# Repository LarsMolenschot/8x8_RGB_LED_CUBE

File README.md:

# 8x8_RGB_LED_CUBE
This is a personal project, the goal of the project is to create a RGB LED cube with the AA0084 RGB LED's.
A custom PCB will be designed for the cube housing a STM32 which can be programmed to display different patterns.
The PCB will include a expansion possibility to house a sd card slot with spi in the future.

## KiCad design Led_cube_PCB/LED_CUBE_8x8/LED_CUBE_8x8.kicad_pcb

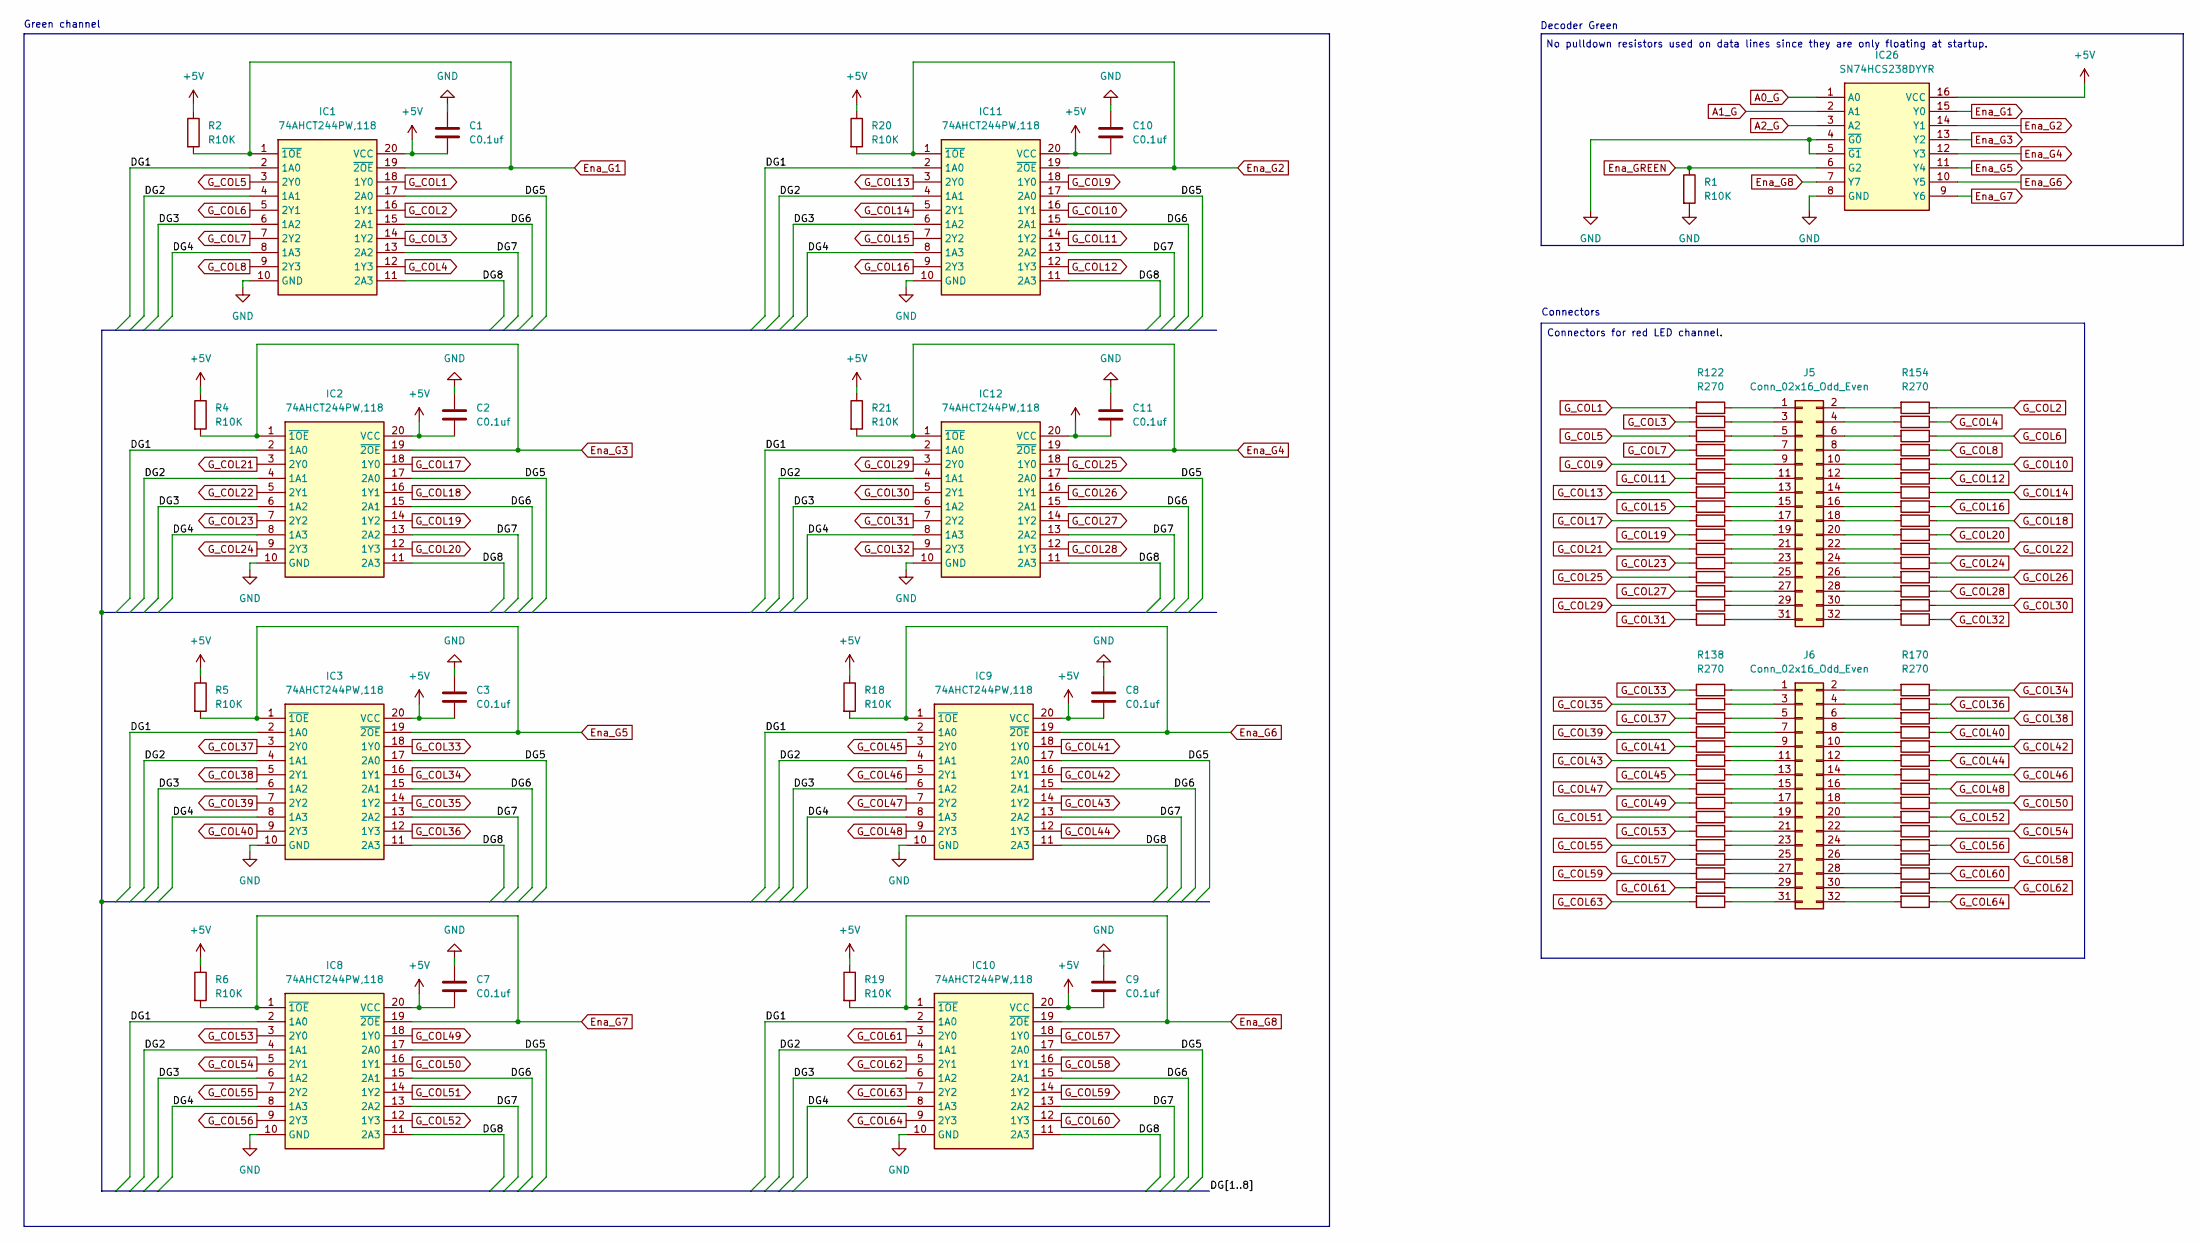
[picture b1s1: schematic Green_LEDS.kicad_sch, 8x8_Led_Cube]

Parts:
C1, C2, C3, C7, C8, C9, C10, C11: C0.1uf; C_0603_1608Metric_Pad1.08x0.95mm_HandSolder
IC1, IC2, IC3, IC8, IC9, IC10, IC11, IC12: 74AHCT244PW,118; SOP65P640X110-20N; Mouser Part Number 771-AHCT244PW118
IC26: SN74HCS238DYYR; SOP50P326X110-16N; Mouser Part Number 595-SN74HCS238DYYR
J5, J6: Conn_02x16_Odd_Even; PinSocket_2x16_P2.54mm_Vertical
R1, R2, R4, R5, R6, R18, R19, R20, R21: R10K; R_0603_1608Metric_Pad0.98x0.95mm_HandSolder
R122, R123, R124, R125, R126, R127, R128, R129, R130, R131, R132, R133, R134, R135, R136, R137, R138, R139, R140, R141, R142, R143, R144, R145, R146, R147, R148, R149, R150, R151, R152, R153, R154, R155, R156, R157, R158, R159, R160, R161, R162, R163, R164, R165, R166, R167, R168, R169, R170, R171, R172, R173, R174, R175, R176, R177, R178, R179, R180, R181, R182, R183, R184, R185: R270; R_0603_1608Metric_Pad0.98x0.95mm_HandSolder

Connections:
+5V: C1.2, C2.2, C3.2, C7.2, C8.2, C9.2, C10.2, C11.2, IC1.20 (VCC), IC2.20 (VCC), IC3.20 (VCC), IC8.20 (VCC), IC9.20 (VCC), IC10.20 (VCC), IC11.20 (VCC), IC12.20 (VCC), IC26.16 (VCC), R2.1, R4.1, R5.1, R6.1, R18.1, R19.1, R20.1, R21.1; also elsewhere on the board
/Green LED's/DG1: IC1.2 (1A0), IC2.2 (1A0), IC3.2 (1A0), IC8.2 (1A0), IC9.2 (1A0), IC10.2 (1A0), IC11.2 (1A0), IC12.2 (1A0)
/Green LED's/DG2: IC1.4 (1A1), IC2.4 (1A1), IC3.4 (1A1), IC8.4 (1A1), IC9.4 (1A1), IC10.4 (1A1), IC11.4 (1A1), IC12.4 (1A1)
/Green LED's/DG3: IC1.6 (1A2), IC2.6 (1A2), IC3.6 (1A2), IC8.6 (1A2), IC9.6 (1A2), IC10.6 (1A2), IC11.6 (1A2), IC12.6 (1A2)
/Green LED's/DG4: IC1.8 (1A3), IC2.8 (1A3), IC3.8 (1A3), IC8.8 (1A3), IC9.8 (1A3), IC10.8 (1A3), IC11.8 (1A3), IC12.8 (1A3)
/Green LED's/DG5: IC1.17 (2A0), IC2.17 (2A0), IC3.17 (2A0), IC8.17 (2A0), IC9.17 (2A0), IC10.17 (2A0), IC11.17 (2A0), IC12.17 (2A0)
/Green LED's/DG6: IC1.15 (2A1), IC2.15 (2A1), IC3.15 (2A1), IC8.15 (2A1), IC9.15 (2A1), IC10.15 (2A1), IC11.15 (2A1), IC12.15 (2A1)
/Green LED's/DG7: IC1.13 (2A2), IC2.13 (2A2), IC3.13 (2A2), IC8.13 (2A2), IC9.13 (2A2), IC10.13 (2A2), IC11.13 (2A2), IC12.13 (2A2)
/Green LED's/DG8: IC1.11 (2A3), IC2.11 (2A3), IC3.11 (2A3), IC8.11 (2A3), IC9.11 (2A3), IC10.11 (2A3), IC11.11 (2A3), IC12.11 (2A3)
A0_G: IC26.1 (A0); also elsewhere on the board
A1_G: IC26.2 (A1); also elsewhere on the board
A2_G: IC26.3 (A2); also elsewhere on the board
Ena_G1: IC1.1 (~1OE), IC1.19 (~2OE), IC26.15 (Y0), R2.2
Ena_G2: IC11.1 (~1OE), IC11.19 (~2OE), IC26.14 (Y1), R20.2
Ena_G3: IC2.1 (~1OE), IC2.19 (~2OE), IC26.13 (Y2), R4.2
Ena_G4: IC12.1 (~1OE), IC12.19 (~2OE), IC26.12 (Y3), R21.2
Ena_G5: IC3.1 (~1OE), IC3.19 (~2OE), IC26.11 (Y4), R5.2
Ena_G6: IC9.1 (~1OE), IC9.19 (~2OE), IC26.10 (Y5), R18.2
Ena_G7: IC8.1 (~1OE), IC8.19 (~2OE), IC26.9 (Y6), R6.2
Ena_G8: IC10.1 (~1OE), IC10.19 (~2OE), IC26.7 (Y7), R19.2
Ena_GREEN: IC26.6 (G2), R1.1
GND: C1.1, C2.1, C3.1, C7.1, C8.1, C9.1, C10.1, C11.1, IC1.10 (GND), IC2.10 (GND), IC3.10 (GND), IC8.10 (GND), IC9.10 (GND), IC10.10 (GND), IC11.10 (GND), IC12.10 (GND), IC26.4 (~G0), IC26.5 (~G1), IC26.8 (GND), R1.2; also elsewhere on the board
G_COL1: IC1.18 (1Y0), R122.2
G_COL2: IC1.16 (1Y1), R154.1
G_COL3: IC1.14 (1Y2), R123.2
G_COL4: IC1.12 (1Y3), R155.1
G_COL5: IC1.3 (2Y0), R124.2
G_COL6: IC1.5 (2Y1), R156.1
G_COL7: IC1.7 (2Y2), R125.2
G_COL8: IC1.9 (2Y3), R157.1
G_COL9: IC11.18 (1Y0), R126.2
G_COL10: IC11.16 (1Y1), R158.1
G_COL11: IC11.14 (1Y2), R127.2
G_COL12: IC11.12 (1Y3), R159.1
G_COL13: IC11.3 (2Y0), R128.2
G_COL14: IC11.5 (2Y1), R160.1
G_COL15: IC11.7 (2Y2), R129.2
G_COL16: IC11.9 (2Y3), R161.1
G_COL17: IC2.18 (1Y0), R130.2
G_COL18: IC2.16 (1Y1), R162.1
G_COL19: IC2.14 (1Y2), R131.2
G_COL20: IC2.12 (1Y3), R163.1
G_COL21: IC2.3 (2Y0), R132.2
G_COL22: IC2.5 (2Y1), R164.1
G_COL23: IC2.7 (2Y2), R133.2
G_COL24: IC2.9 (2Y3), R165.1
G_COL25: IC12.18 (1Y0), R134.2
G_COL26: IC12.16 (1Y1), R166.1
G_COL27: IC12.14 (1Y2), R135.2
G_COL28: IC12.12 (1Y3), R167.1
G_COL29: IC12.3 (2Y0), R136.2
G_COL30: IC12.5 (2Y1), R168.1
G_COL31: IC12.7 (2Y2), R137.2
G_COL32: IC12.9 (2Y3), R169.1
G_COL33: IC3.18 (1Y0), R138.2
G_COL34: IC3.16 (1Y1), R170.1
G_COL35: IC3.14 (1Y2), R139.2
G_COL36: IC3.12 (1Y3), R171.1
G_COL37: IC3.3 (2Y0), R140.2
G_COL38: IC3.5 (2Y1), R172.1
G_COL39: IC3.7 (2Y2), R141.2
G_COL40: IC3.9 (2Y3), R173.1
G_COL41: IC9.18 (1Y0), R142.2
G_COL42: IC9.16 (1Y1), R174.1
G_COL43: IC9.14 (1Y2), R143.2
G_COL44: IC9.12 (1Y3), R175.1
G_COL45: IC9.3 (2Y0), R144.2
G_COL46: IC9.5 (2Y1), R176.1
G_COL47: IC9.7 (2Y2), R145.2
G_COL48: IC9.9 (2Y3), R177.1
G_COL49: IC8.18 (1Y0), R146.2
G_COL50: IC8.16 (1Y1), R178.1
G_COL51: IC8.14 (1Y2), R147.2
G_COL52: IC8.12 (1Y3), R179.1
G_COL53: IC8.3 (2Y0), R148.2
G_COL54: IC8.5 (2Y1), R180.1
G_COL55: IC8.7 (2Y2), R149.2
G_COL56: IC8.9 (2Y3), R181.1
G_COL57: IC10.18 (1Y0), R150.2
G_COL58: IC10.16 (1Y1), R182.1
G_COL59: IC10.14 (1Y2), R151.2
G_COL60: IC10.12 (1Y3), R183.1
G_COL61: IC10.3 (2Y0), R152.2
G_COL62: IC10.5 (2Y1), R184.1
G_COL63: IC10.7 (2Y2), R153.2
G_COL64: IC10.9 (2Y3), R185.1
unnamed: J5.1, R122.1
unnamed: J5.2, R154.2
unnamed: J5.3, R123.1
unnamed: J5.4, R155.2
unnamed: J5.5, R124.1
unnamed: J5.6, R156.2
unnamed: J5.7, R125.1
unnamed: J5.8, R157.2
unnamed: J5.9, R126.1
unnamed: J5.10, R158.2
unnamed: J5.11, R127.1
unnamed: J5.12, R159.2
unnamed: J5.13, R128.1
unnamed: J5.14, R160.2
unnamed: J5.15, R129.1
unnamed: J5.16, R161.2
unnamed: J5.17, R130.1
unnamed: J5.18, R162.2
unnamed: J5.19, R131.1
unnamed: J5.20, R163.2
unnamed: J5.21, R132.1
unnamed: J5.22, R164.2
unnamed: J5.23, R133.1
unnamed: J5.24, R165.2
unnamed: J5.25, R134.1
unnamed: J5.26, R166.2
unnamed: J5.27, R135.1
unnamed: J5.28, R167.2
unnamed: J5.29, R136.1
unnamed: J5.30, R168.2
unnamed: J5.31, R137.1
unnamed: J5.32, R169.2
unnamed: J6.1, R138.1
unnamed: J6.2, R170.2
unnamed: J6.3, R139.1
unnamed: J6.4, R171.2
unnamed: J6.5, R140.1
unnamed: J6.6, R172.2
unnamed: J6.7, R141.1
unnamed: J6.8, R173.2
unnamed: J6.9, R142.1
unnamed: J6.10, R174.2
unnamed: J6.11, R143.1
unnamed: J6.12, R175.2
unnamed: J6.13, R144.1
unnamed: J6.14, R176.2
unnamed: J6.15, R145.1
unnamed: J6.16, R177.2
unnamed: J6.17, R146.1
unnamed: J6.18, R178.2
unnamed: J6.19, R147.1
unnamed: J6.20, R179.2
unnamed: J6.21, R148.1
unnamed: J6.22, R180.2
unnamed: J6.23, R149.1
unnamed: J6.24, R181.2
unnamed: J6.25, R150.1
unnamed: J6.26, R182.2
unnamed: J6.27, R151.1
unnamed: J6.28, R183.2
unnamed: J6.29, R152.1
unnamed: J6.30, R184.2
unnamed: J6.31, R153.1
unnamed: J6.32, R185.2

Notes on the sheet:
Connectors
Decoder Green
No pulldown resistors used on data lines since they are only floating at startup.
Green channel
Connectors for red LED channel.

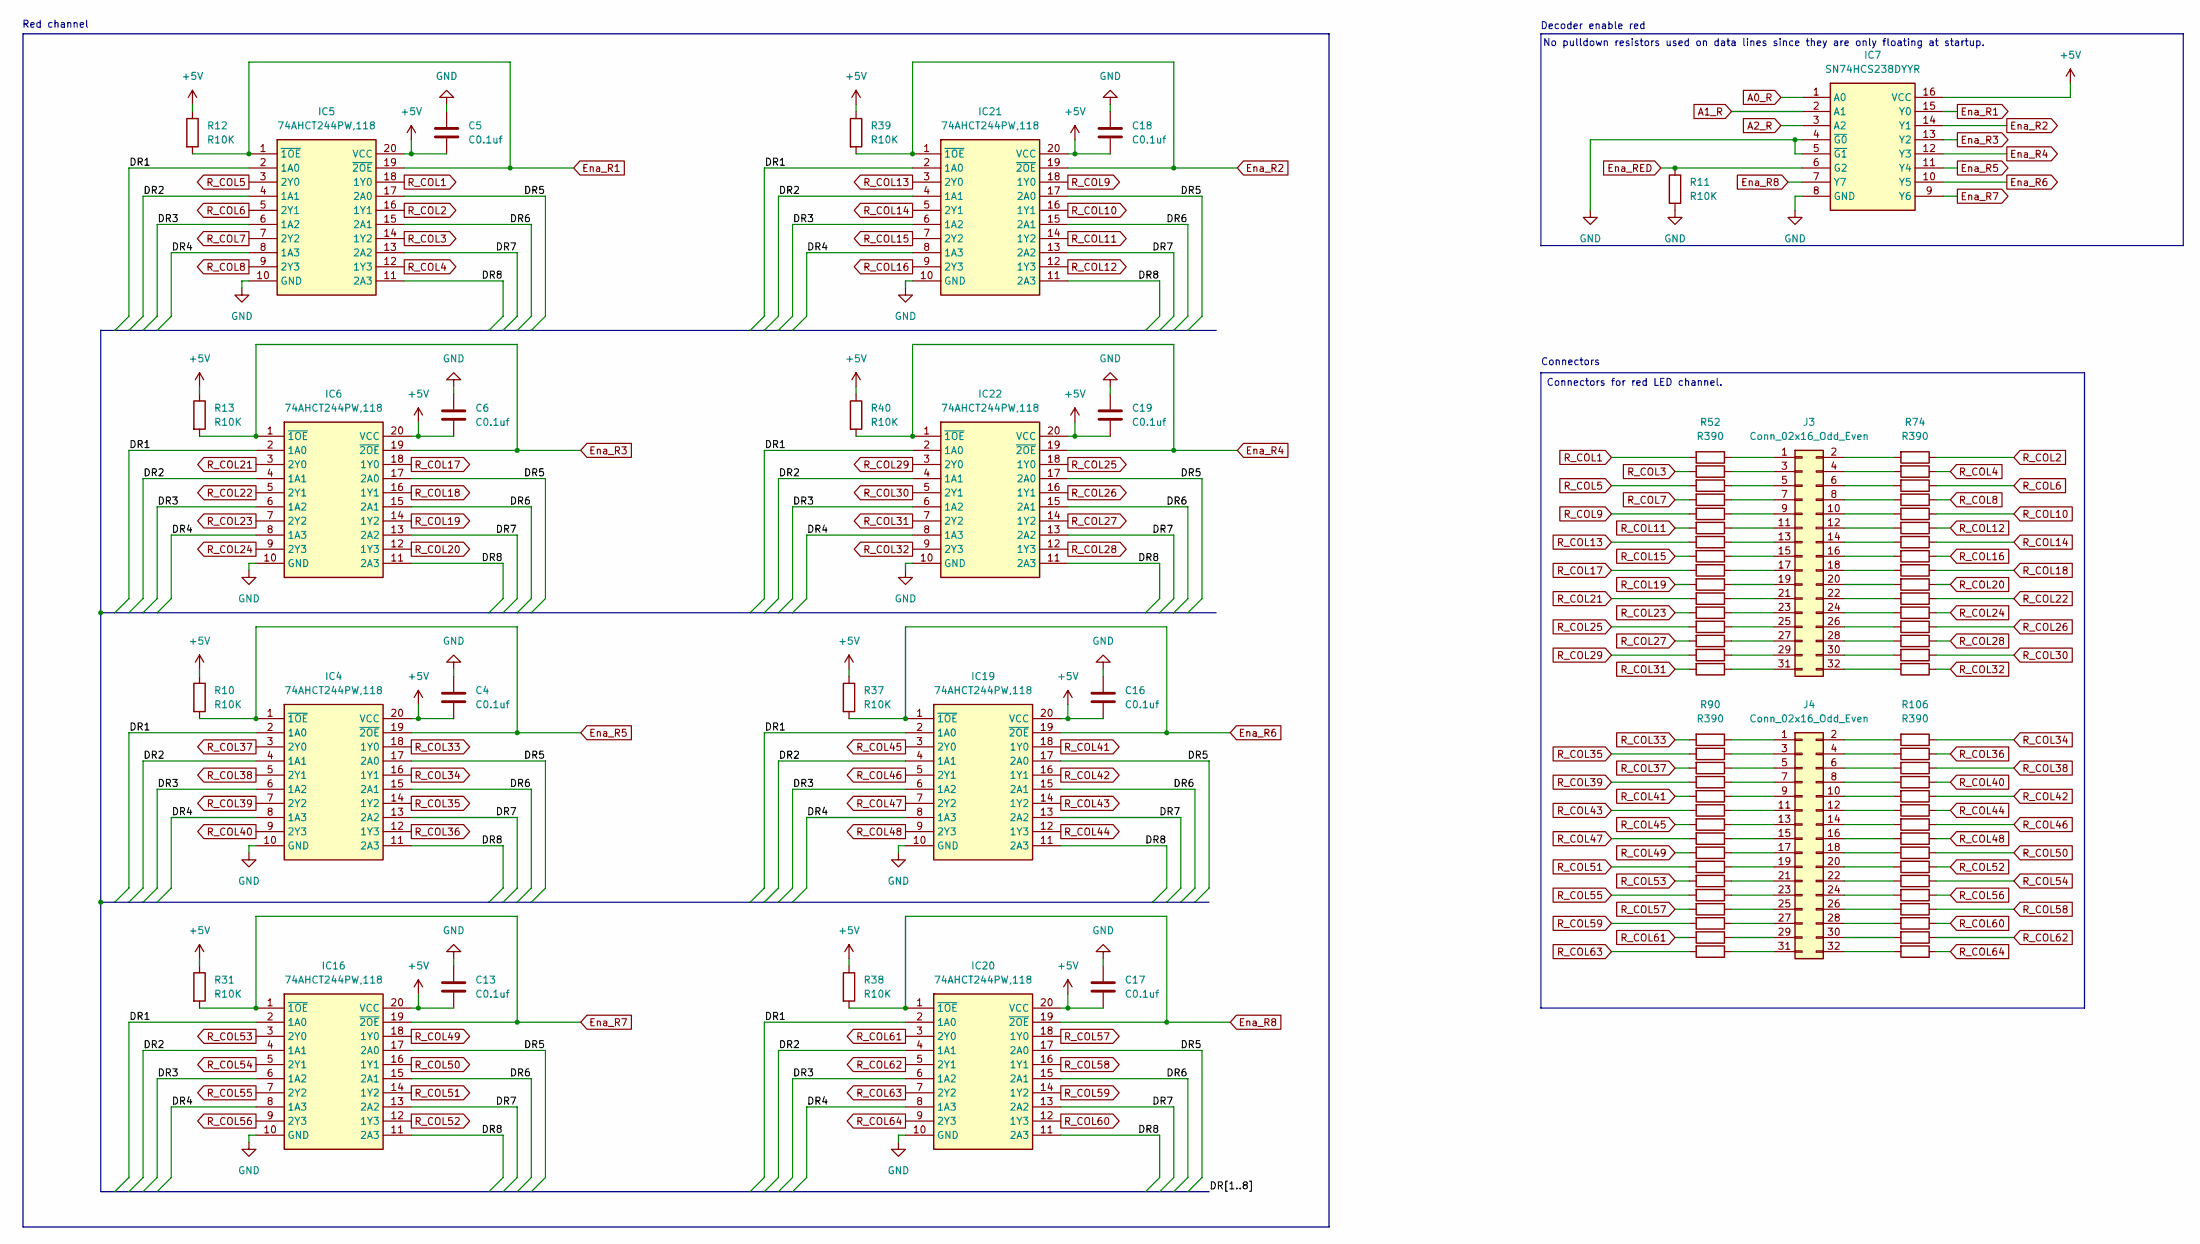
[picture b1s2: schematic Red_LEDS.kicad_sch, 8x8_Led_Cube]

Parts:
C4, C5, C6, C13, C16, C17, C18, C19: C0.1uf; C_0603_1608Metric_Pad1.08x0.95mm_HandSolder
IC4, IC5, IC6, IC16, IC19, IC20, IC21, IC22: 74AHCT244PW,118; SOP65P640X110-20N; Mouser Part Number 771-AHCT244PW118
IC7: SN74HCS238DYYR; SOP50P326X110-16N; Mouser Part Number 595-SN74HCS238DYYR
J3, J4: Conn_02x16_Odd_Even; PinSocket_2x16_P2.54mm_Vertical
R10, R11, R12, R13, R31, R37, R38, R39, R40: R10K; R_0603_1608Metric_Pad0.98x0.95mm_HandSolder
R52, R53, R60, R61, R62, R63, R64, R65, R66, R67, R68, R69, R70, R71, R72, R73, R74, R75, R76, R77, R78, R79, R80, R81, R82, R83, R84, R85, R86, R87, R88, R89, R90, R91, R92, R93, R94, R95, R96, R97, R98, R99, R100, R101, R102, R103, R104, R105, R106, R107, R108, R109, R110, R111, R112, R113, R114, R115, R116, R117, R118, R119, R120, R121: R390; R_0603_1608Metric_Pad0.98x0.95mm_HandSolder

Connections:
+5V: C4.2, C5.2, C6.2, C13.2, C16.2, C17.2, C18.2, C19.2, IC4.20 (VCC), IC5.20 (VCC), IC6.20 (VCC), IC7.16 (VCC), IC16.20 (VCC), IC19.20 (VCC), IC20.20 (VCC), IC21.20 (VCC), IC22.20 (VCC), R10.1, R12.1, R13.1, R31.1, R37.1, R38.1, R39.1, R40.1; also elsewhere on the board
/Red LED's/DR1: IC4.2 (1A0), IC5.2 (1A0), IC6.2 (1A0), IC16.2 (1A0), IC19.2 (1A0), IC20.2 (1A0), IC21.2 (1A0), IC22.2 (1A0)
/Red LED's/DR2: IC4.4 (1A1), IC5.4 (1A1), IC6.4 (1A1), IC16.4 (1A1), IC19.4 (1A1), IC20.4 (1A1), IC21.4 (1A1), IC22.4 (1A1)
/Red LED's/DR3: IC4.6 (1A2), IC5.6 (1A2), IC6.6 (1A2), IC16.6 (1A2), IC19.6 (1A2), IC20.6 (1A2), IC21.6 (1A2), IC22.6 (1A2)
/Red LED's/DR4: IC4.8 (1A3), IC5.8 (1A3), IC6.8 (1A3), IC16.8 (1A3), IC19.8 (1A3), IC20.8 (1A3), IC21.8 (1A3), IC22.8 (1A3)
/Red LED's/DR5: IC4.17 (2A0), IC5.17 (2A0), IC6.17 (2A0), IC16.17 (2A0), IC19.17 (2A0), IC20.17 (2A0), IC21.17 (2A0), IC22.17 (2A0)
/Red LED's/DR6: IC4.15 (2A1), IC5.15 (2A1), IC6.15 (2A1), IC16.15 (2A1), IC19.15 (2A1), IC20.15 (2A1), IC21.15 (2A1), IC22.15 (2A1)
/Red LED's/DR7: IC4.13 (2A2), IC5.13 (2A2), IC6.13 (2A2), IC16.13 (2A2), IC19.13 (2A2), IC20.13 (2A2), IC21.13 (2A2), IC22.13 (2A2)
/Red LED's/DR8: IC4.11 (2A3), IC5.11 (2A3), IC6.11 (2A3), IC16.11 (2A3), IC19.11 (2A3), IC20.11 (2A3), IC21.11 (2A3), IC22.11 (2A3)
A0_R: IC7.1 (A0); also elsewhere on the board
A1_R: IC7.2 (A1); also elsewhere on the board
A2_R: IC7.3 (A2); also elsewhere on the board
Ena_R1: IC5.1 (~1OE), IC5.19 (~2OE), IC7.15 (Y0), R12.2
Ena_R2: IC7.14 (Y1), IC21.1 (~1OE), IC21.19 (~2OE), R39.2
Ena_R3: IC6.1 (~1OE), IC6.19 (~2OE), IC7.13 (Y2), R13.2
Ena_R4: IC7.12 (Y3), IC22.1 (~1OE), IC22.19 (~2OE), R40.2
Ena_R5: IC4.1 (~1OE), IC4.19 (~2OE), IC7.11 (Y4), R10.2
Ena_R6: IC7.10 (Y5), IC19.1 (~1OE), IC19.19 (~2OE), R37.2
Ena_R7: IC7.9 (Y6), IC16.1 (~1OE), IC16.19 (~2OE), R31.2
Ena_R8: IC7.7 (Y7), IC20.1 (~1OE), IC20.19 (~2OE), R38.2
Ena_RED: IC7.6 (G2), R11.1
GND: C4.1, C5.1, C6.1, C13.1, C16.1, C17.1, C18.1, C19.1, IC4.10 (GND), IC5.10 (GND), IC6.10 (GND), IC7.4 (~G0), IC7.5 (~G1), IC7.8 (GND), IC16.10 (GND), IC19.10 (GND), IC20.10 (GND), IC21.10 (GND), IC22.10 (GND), R11.2; also elsewhere on the board
unnamed: J3.1, R52.1
unnamed: J3.2, R74.2
unnamed: J3.3, R53.1
unnamed: J3.4, R75.2
unnamed: J3.5, R60.1
unnamed: J3.6, R76.2
unnamed: J3.7, R61.1
unnamed: J3.8, R77.2
unnamed: J3.9, R62.1
unnamed: J3.10, R78.2
unnamed: J3.11, R63.1
unnamed: J3.12, R79.2
unnamed: J3.13, R64.1
unnamed: J3.14, R80.2
unnamed: J3.15, R65.1
unnamed: J3.16, R81.2
unnamed: J3.17, R66.1
unnamed: J3.18, R82.2
unnamed: J3.19, R67.1
unnamed: J3.20, R83.2
unnamed: J3.21, R68.1
unnamed: J3.22, R84.2
unnamed: J3.23, R69.1
unnamed: J3.24, R85.2
unnamed: J3.25, R70.1
unnamed: J3.26, R86.2
unnamed: J3.27, R71.1
unnamed: J3.28, R87.2
unnamed: J3.29, R72.1
unnamed: J3.30, R88.2
unnamed: J3.31, R73.1
unnamed: J3.32, R89.2
unnamed: J4.1, R90.1
unnamed: J4.2, R106.2
unnamed: J4.3, R91.1
unnamed: J4.4, R107.2
unnamed: J4.5, R92.1
unnamed: J4.6, R108.2
unnamed: J4.7, R93.1
unnamed: J4.8, R109.2
unnamed: J4.9, R94.1
unnamed: J4.10, R110.2
unnamed: J4.11, R95.1
unnamed: J4.12, R111.2
unnamed: J4.13, R96.1
unnamed: J4.14, R112.2
unnamed: J4.15, R97.1
unnamed: J4.16, R113.2
unnamed: J4.17, R98.1
unnamed: J4.18, R114.2
unnamed: J4.19, R99.1
unnamed: J4.20, R115.2
unnamed: J4.21, R100.1
unnamed: J4.22, R116.2
unnamed: J4.23, R101.1
unnamed: J4.24, R117.2
unnamed: J4.25, R102.1
unnamed: J4.26, R118.2
unnamed: J4.27, R103.1
unnamed: J4.28, R119.2
unnamed: J4.29, R104.1
unnamed: J4.30, R120.2
unnamed: J4.31, R105.1
unnamed: J4.32, R121.2
R_COL1: IC5.18 (1Y0), R52.2
R_COL2: IC5.16 (1Y1), R74.1
R_COL3: IC5.14 (1Y2), R53.2
R_COL4: IC5.12 (1Y3), R75.1
R_COL5: IC5.3 (2Y0), R60.2
R_COL6: IC5.5 (2Y1), R76.1
R_COL7: IC5.7 (2Y2), R61.2
R_COL8: IC5.9 (2Y3), R77.1
R_COL9: IC21.18 (1Y0), R62.2
R_COL10: IC21.16 (1Y1), R78.1
R_COL11: IC21.14 (1Y2), R63.2
R_COL12: IC21.12 (1Y3), R79.1
R_COL13: IC21.3 (2Y0), R64.2
R_COL14: IC21.5 (2Y1), R80.1
R_COL15: IC21.7 (2Y2), R65.2
R_COL16: IC21.9 (2Y3), R81.1
R_COL17: IC6.18 (1Y0), R66.2
R_COL18: IC6.16 (1Y1), R82.1
R_COL19: IC6.14 (1Y2), R67.2
R_COL20: IC6.12 (1Y3), R83.1
R_COL21: IC6.3 (2Y0), R68.2
R_COL22: IC6.5 (2Y1), R84.1
R_COL23: IC6.7 (2Y2), R69.2
R_COL24: IC6.9 (2Y3), R85.1
R_COL25: IC22.18 (1Y0), R70.2
R_COL26: IC22.16 (1Y1), R86.1
R_COL27: IC22.14 (1Y2), R71.2
R_COL28: IC22.12 (1Y3), R87.1
R_COL29: IC22.3 (2Y0), R72.2
R_COL30: IC22.5 (2Y1), R88.1
R_COL31: IC22.7 (2Y2), R73.2
R_COL32: IC22.9 (2Y3), R89.1
R_COL33: IC4.18 (1Y0), R90.2
R_COL34: IC4.16 (1Y1), R106.1
R_COL35: IC4.14 (1Y2), R91.2
R_COL36: IC4.12 (1Y3), R107.1
R_COL37: IC4.3 (2Y0), R92.2
R_COL38: IC4.5 (2Y1), R108.1
R_COL39: IC4.7 (2Y2), R93.2
R_COL40: IC4.9 (2Y3), R109.1
R_COL41: IC19.18 (1Y0), R94.2
R_COL42: IC19.16 (1Y1), R110.1
R_COL43: IC19.14 (1Y2), R95.2
R_COL44: IC19.12 (1Y3), R111.1
R_COL45: IC19.3 (2Y0), R96.2
R_COL46: IC19.5 (2Y1), R112.1
R_COL47: IC19.7 (2Y2), R97.2
R_COL48: IC19.9 (2Y3), R113.1
R_COL49: IC16.18 (1Y0), R98.2
R_COL50: IC16.16 (1Y1), R114.1
R_COL51: IC16.14 (1Y2), R99.2
R_COL52: IC16.12 (1Y3), R115.1
R_COL53: IC16.3 (2Y0), R100.2
R_COL54: IC16.5 (2Y1), R116.1
R_COL55: IC16.7 (2Y2), R101.2
R_COL56: IC16.9 (2Y3), R117.1
R_COL57: IC20.18 (1Y0), R102.2
R_COL58: IC20.16 (1Y1), R118.1
R_COL59: IC20.14 (1Y2), R103.2
R_COL60: IC20.12 (1Y3), R119.1
R_COL61: IC20.3 (2Y0), R104.2
R_COL62: IC20.5 (2Y1), R120.1
R_COL63: IC20.7 (2Y2), R105.2
R_COL64: IC20.9 (2Y3), R121.1

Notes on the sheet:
Connectors
Red channel
No pulldown resistors used on data lines since they are only floating at startup.
Decoder enable red
Connectors for red LED channel.

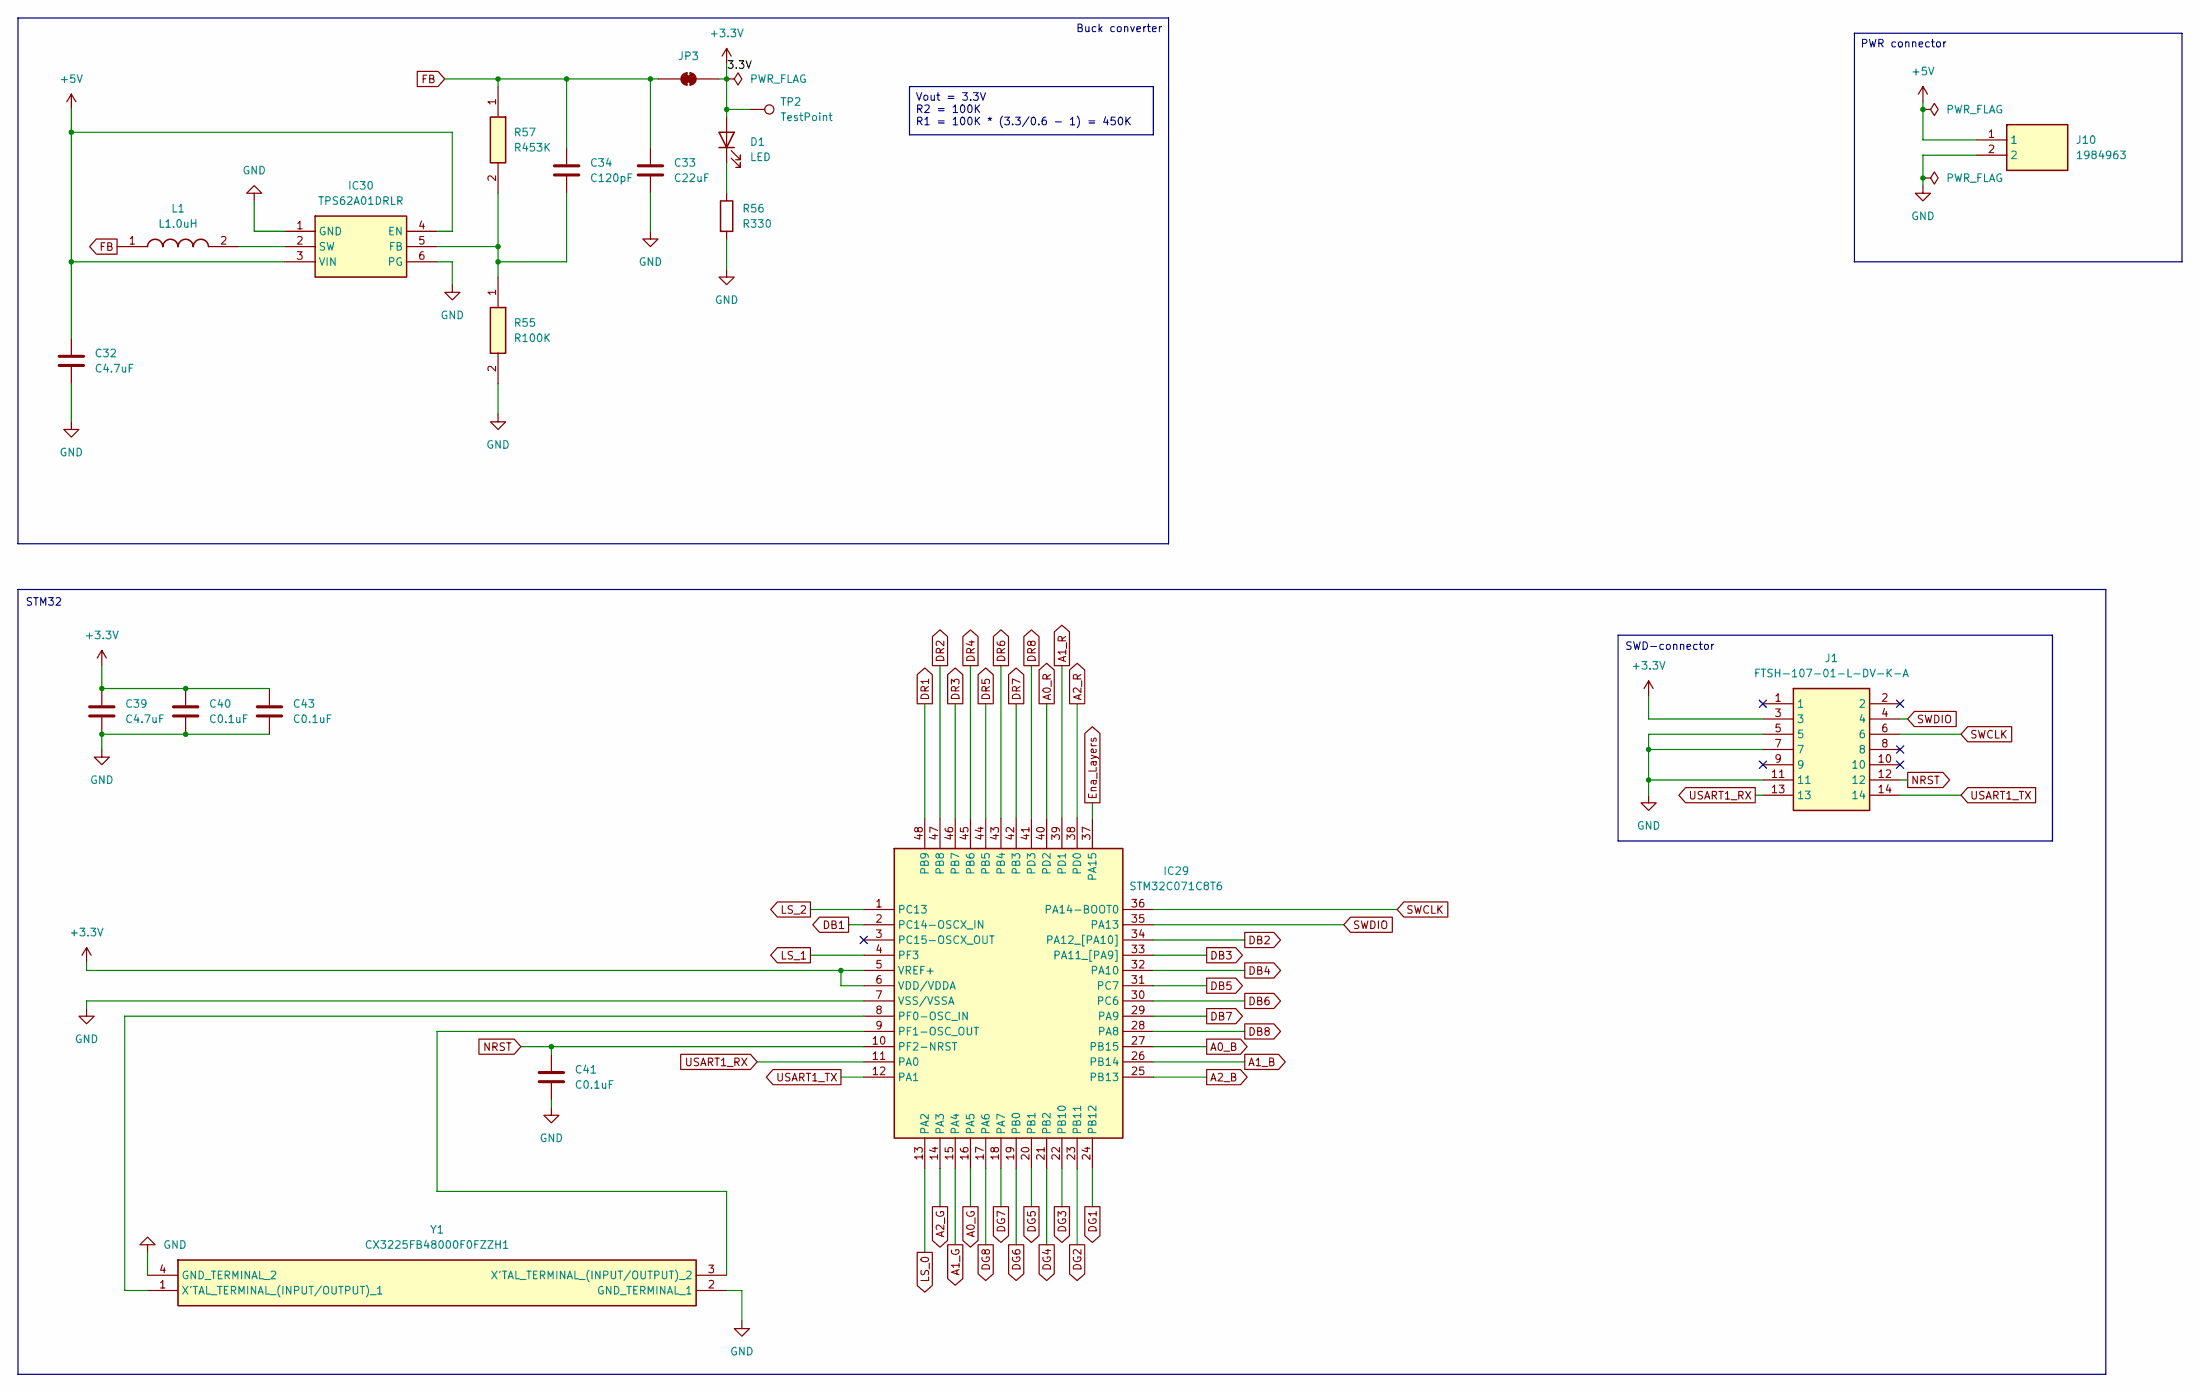
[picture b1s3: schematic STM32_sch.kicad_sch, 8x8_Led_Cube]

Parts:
C32, C39: C4.7uF; C_0603_1608Metric_Pad1.08x0.95mm_HandSolder
C33: C22uF; C_0603_1608Metric_Pad1.08x0.95mm_HandSolder
C34: C120pF; C_0603_1608Metric_Pad1.08x0.95mm_HandSolder
C40, C41, C43: C0.1uF; C_0603_1608Metric_Pad1.08x0.95mm_HandSolder
D1: LED; LED_0805_2012Metric_Pad1.15x1.40mm_HandSolder
IC29: STM32C071C8T6; QFP50P900X900X160-48N; Mouser Part Number 511-STM32C071C8T6
IC30: TPS62A01DRLR; SOTFL50P160X60-6N; Mouser Part Number 595-TPS62A01DRLR
J1: FTSH-107-01-L-DV-K-A; FTSH-107-XX-YYY-DV-K-A; Mouser Part Number 200-FTSH10701LDVKA
J10: 1984963; Mouser Part Number 651-1984963
JP3: SolderJumper_2_Bridged; SolderJumper-2_P1.3mm_Open_RoundedPad1.0x1.5mm
L1: L1.0uH; DFE2HCAH1R0MJ0L; Mouser Part Number 81-DFE252012F-1R0MP2
R55: R100K; R_0603_1608Metric_Pad0.98x0.95mm_HandSolder; Mouser Part Number 603-SR0603FR-07100KL
R56: R330; R_0603_1608Metric_Pad0.98x0.95mm_HandSolder
R57: R453K; R_0603_1608Metric_Pad0.98x0.95mm_HandSolder; Mouser Part Number 603-AF0603FR-07453KL
TP2: TestPoint; TestPoint_Pad_D2.0mm
Y1: CX3225FB48000F0FZZH1; Manufacturer_Part_Number CX3225FB48000F0FZZH1

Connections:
+3.3V: C39.1, C40.1, C43.1, D1.2 (A), IC29.5 (VREF+), IC29.6 (VDD/VDDA), J1.3, JP3.1 (A), TP2.1 (1_1); also elsewhere on the board
+5V: C32.1, IC30.3 (VIN), IC30.4 (EN), J10.1; also elsewhere on the board
A0_B: IC29.27 (PB15); also elsewhere on the board
A0_G: IC29.16 (PA5); also elsewhere on the board
A0_R: IC29.40 (PD2); also elsewhere on the board
A1_B: IC29.26 (PB14); also elsewhere on the board
A1_G: IC29.15 (PA4); also elsewhere on the board
A1_R: IC29.39 (PD1); also elsewhere on the board
A2_B: IC29.25 (PB13); also elsewhere on the board
A2_G: IC29.14 (PA3); also elsewhere on the board
A2_R: IC29.38 (PD0); also elsewhere on the board
DB1: IC29.2 (PC14-OSCX_IN)
DB2: IC29.34 (PA12_[PA10])
DB3: IC29.33 (PA11_[PA9])
DB4: IC29.32 (PA10)
DB5: IC29.31 (PC7)
DB6: IC29.30 (PC6)
DB7: IC29.29 (PA9)
DB8: IC29.28 (PA8)
DG1: IC29.24 (PB12)
DG2: IC29.23 (PB11)
DG3: IC29.22 (PB10)
DG4: IC29.21 (PB2)
DG5: IC29.20 (PB1)
DG6: IC29.19 (PB0)
DG7: IC29.18 (PA7)
DG8: IC29.17 (PA6)
DR1: IC29.48 (PB9)
DR2: IC29.47 (PB8)
DR3: IC29.46 (PB7)
DR4: IC29.45 (PB6)
DR5: IC29.44 (PB5)
DR6: IC29.43 (PB4)
DR7: IC29.42 (PB3)
DR8: IC29.41 (PD3)
Ena_Layers: IC29.37 (PA15); also elsewhere on the board
FB: C33.1, C34.1, JP3.2 (B), L1.1, R57.1
GND: C32.2, C33.2, C39.2, C40.2, C41.2, C43.2, IC29.7 (VSS/VSSA), IC30.1 (GND), IC30.6 (PG), J1.5, J1.7, J1.11, J10.2, R55.2, R56.2, Y1.2 (GND_TERMINAL_1), Y1.4 (GND_TERMINAL_2); also elsewhere on the board
LS_0: IC29.13 (PA2); also elsewhere on the board
LS_1: IC29.4 (PF3); also elsewhere on the board
LS_2: IC29.1 (PC13); also elsewhere on the board
NRST: C41.1, IC29.10 (PF2-NRST), J1.12; also elsewhere on the board
unnamed: D1.1 (K), R56.1
unnamed: IC29.8 (PF0-OSC_IN), Y1.1 (X'TAL_TERMINAL_(INPUT/OUTPUT)_1)
unnamed: IC29.9 (PF1-OSC_OUT), Y1.3 (X'TAL_TERMINAL_(INPUT/OUTPUT)_2)
unnamed: C34.2, IC30.5 (FB), R55.1, R57.2
unnamed: IC30.2 (SW), L1.2
SWCLK: IC29.36 (PA14-BOOT0), J1.6
SWDIO: IC29.35 (PA13), J1.4

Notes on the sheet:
SWD-connector
STM32
Vout = 3.3V R2 = 100K R1 = 100K * (3.3/0.6 - 1) = 450K
PWR connector
Buck converter

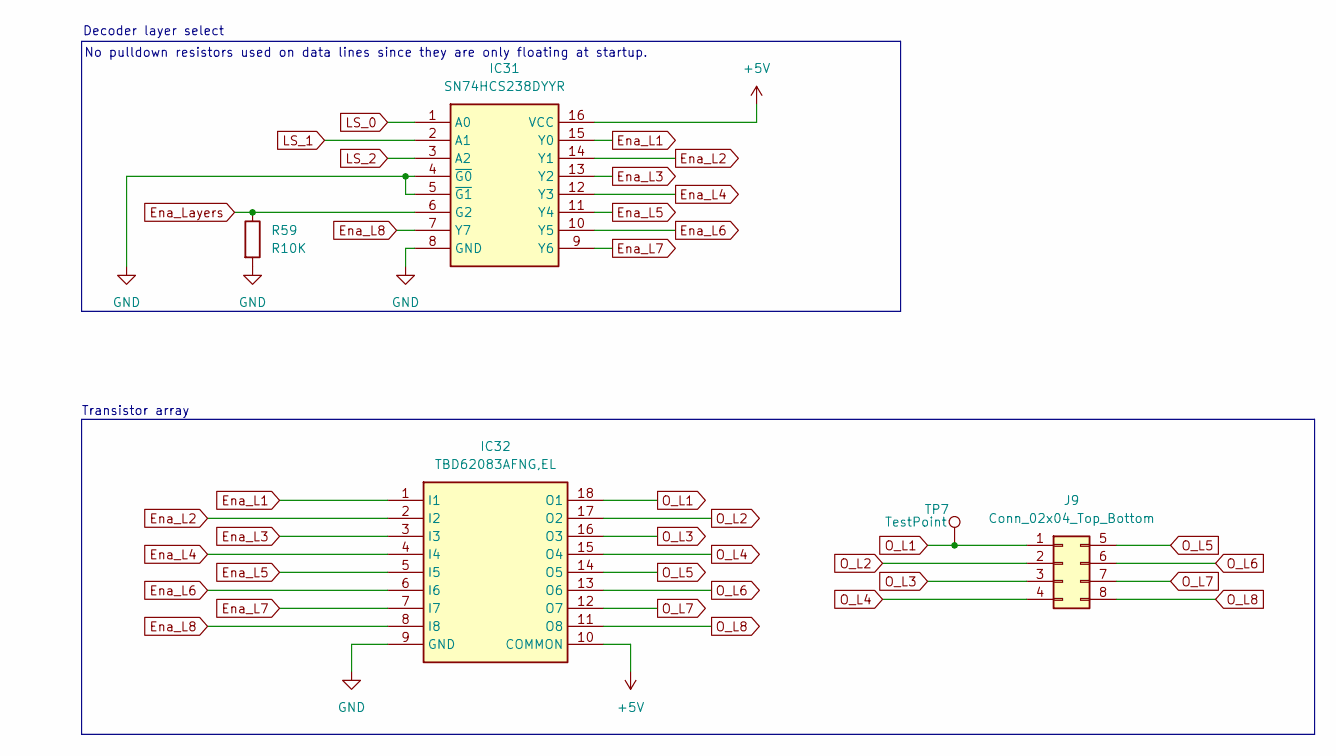
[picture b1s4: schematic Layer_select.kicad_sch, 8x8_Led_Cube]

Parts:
IC31: SN74HCS238DYYR; SOP50P326X110-16N; Mouser Part Number 595-SN74HCS238DYYR
IC32: TBD62083AFNG,EL; SOIC127P1030X245-18N; Mouser Part Number 757-TBD62083AFNGEL
J9: Conn_02x04_Top_Bottom; PinHeader_2x04_P2.54mm_Vertical
R59: R10K; R_0603_1608Metric_Pad0.98x0.95mm_HandSolder
TP7: TestPoint; TestPoint_Pad_D2.0mm

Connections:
+5V: IC31.16 (VCC), IC32.10 (COMMON); also elsewhere on the board
Ena_L1: IC31.15 (Y0), IC32.1 (I1)
Ena_L2: IC31.14 (Y1), IC32.2 (I2)
Ena_L3: IC31.13 (Y2), IC32.3 (I3)
Ena_L4: IC31.12 (Y3), IC32.4 (I4)
Ena_L5: IC31.11 (Y4), IC32.5 (I5)
Ena_L6: IC31.10 (Y5), IC32.6 (I6)
Ena_L7: IC31.9 (Y6), IC32.7 (I7)
Ena_L8: IC31.7 (Y7), IC32.8 (I8)
Ena_Layers: IC31.6 (G2), R59.1; also elsewhere on the board
GND: IC31.4 (~G0), IC31.5 (~G1), IC31.8 (GND), IC32.9 (GND), R59.2; also elsewhere on the board
LS_0: IC31.1 (A0); also elsewhere on the board
LS_1: IC31.2 (A1); also elsewhere on the board
LS_2: IC31.3 (A2); also elsewhere on the board
O_L1: IC32.18 (O1), J9.1, TP7.1 (1_1)
O_L2: IC32.17 (O2), J9.2
O_L3: IC32.16 (O3), J9.3
O_L4: IC32.15 (O4), J9.4
O_L5: IC32.14 (O5), J9.5
O_L6: IC32.13 (O6), J9.6
O_L7: IC32.12 (O7), J9.7
O_L8: IC32.11 (O8), J9.8

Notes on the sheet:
No pulldown resistors used on data lines since they are only floating at startup.
Transistor array
Decoder layer select
